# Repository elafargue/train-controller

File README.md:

train-controller
================

A Z scale model train controller with web interface.

You will find detailed instructions at http://www.aerodynes.org/ . This repository includes both hardware design files and the software you need to build the complete project.

The whole system is working well, and has been running for a long time on an actual layout.

Repository structure:

arduino: arduino sketches for the train controller hardware
hardware: schematics, boards (Eagle)
server: the node.js server that interfaces with the controller and serves the web app

Installation:

Please refer to http://www.aerodynes.org/ for detailed installation instructions. Below is a quick summary:

- Build the cape - Eagle files are included, all components are referenced in the design file, it is fairly straightforward.
- Install the arduino firmware on the cape: you can use the very good "ino" command line interface for doing so.
- Install Ubuntu Linux on your Beaglebone Black
- Install the latest nodejs distribution, and clone this repository
- Install mongodb (Ubuntu package is fine)
- Run "npm install" then "node server.js"
- ... you should be set!

Credits:

Thanks to the creators of the PID and aJson libraries (be sure to use the latest aJson library as I contributed patches to make it more robust).
Thanks to Christophe Coenraets for his great tutorials which were used as a base for the server

License:

All original code is placed under GPLv3 unless stated otherwise, see relevant license files where appropriate.

# Run as a service

Use `resources/train-controller.service` and copy it to `/etc/systemd/system`, then:

```
$ sudo systemctl daemon-reload
$ sudo systemctl enable train-controller
Created symlink /etc/systemd/system/multi-user.target.wants/train-controller.service → /etc/systemd/system/train-controller.service.
$ sudo service train-controller start
```

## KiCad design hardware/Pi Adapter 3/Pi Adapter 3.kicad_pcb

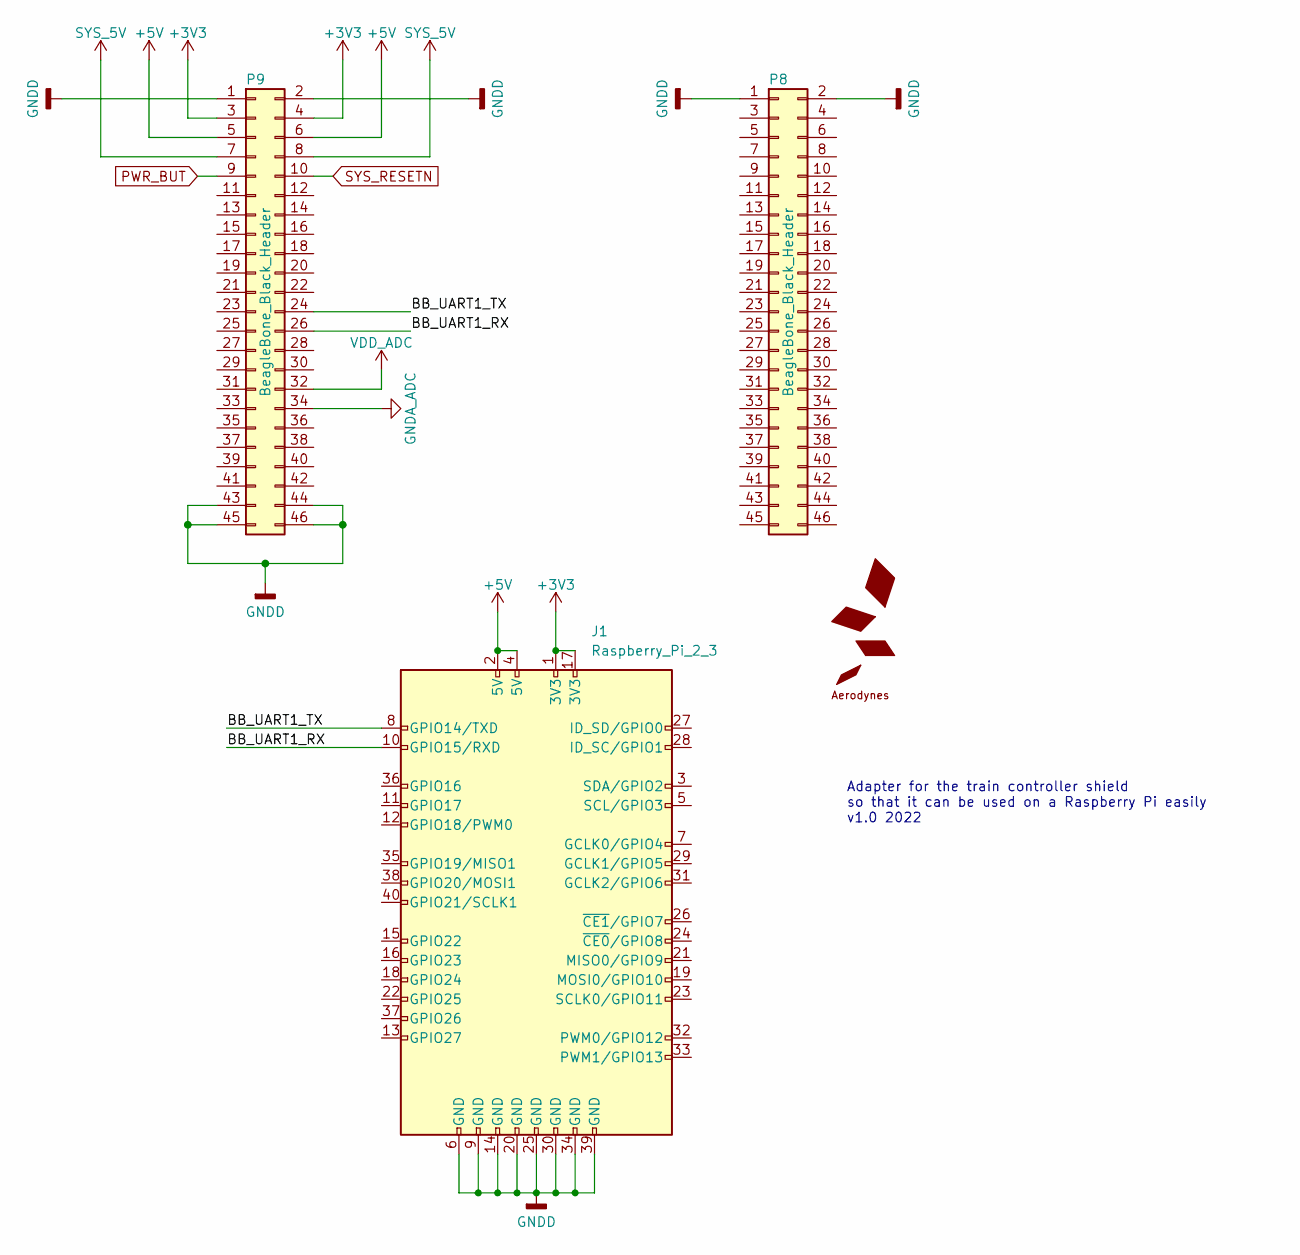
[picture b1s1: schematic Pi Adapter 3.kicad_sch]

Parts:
J1: Raspberry_Pi_2_3; PinSocket_2x20_P2.54mm_Vertical
M1: LOGO-AERODYNESSMALL; LOGO-AERODYNES-S
P8, P9: BeagleBone_Black_Header; Socket_BeagleBone_Black

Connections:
+3V3: J1.1 (3V3), J1.17 (3V3), P9.3, P9.4
+5V: J1.2 (5V), J1.4 (5V), P9.5, P9.6
/BB_UART1_RX: J1.10 (GPIO15/RXD), P9.26
/BB_UART1_TX: J1.8 (GPIO14/TXD), P9.24
GNDA_ADC: P9.34
GNDD: J1.6 (GND), J1.9 (GND), J1.14 (GND), J1.20 (GND), J1.25 (GND), J1.30 (GND), J1.34 (GND), J1.39 (GND), P8.1, P8.2, P9.1, P9.2, P9.43, P9.44, P9.45, P9.46
PWR_BUT: P9.9
SYS_5V: P9.7, P9.8
SYS_RESETN: P9.10
VDD_ADC: P9.32

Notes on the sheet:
Adapter for the train controller shield so that it can be used on a Raspberry Pi easily v1.0 2022

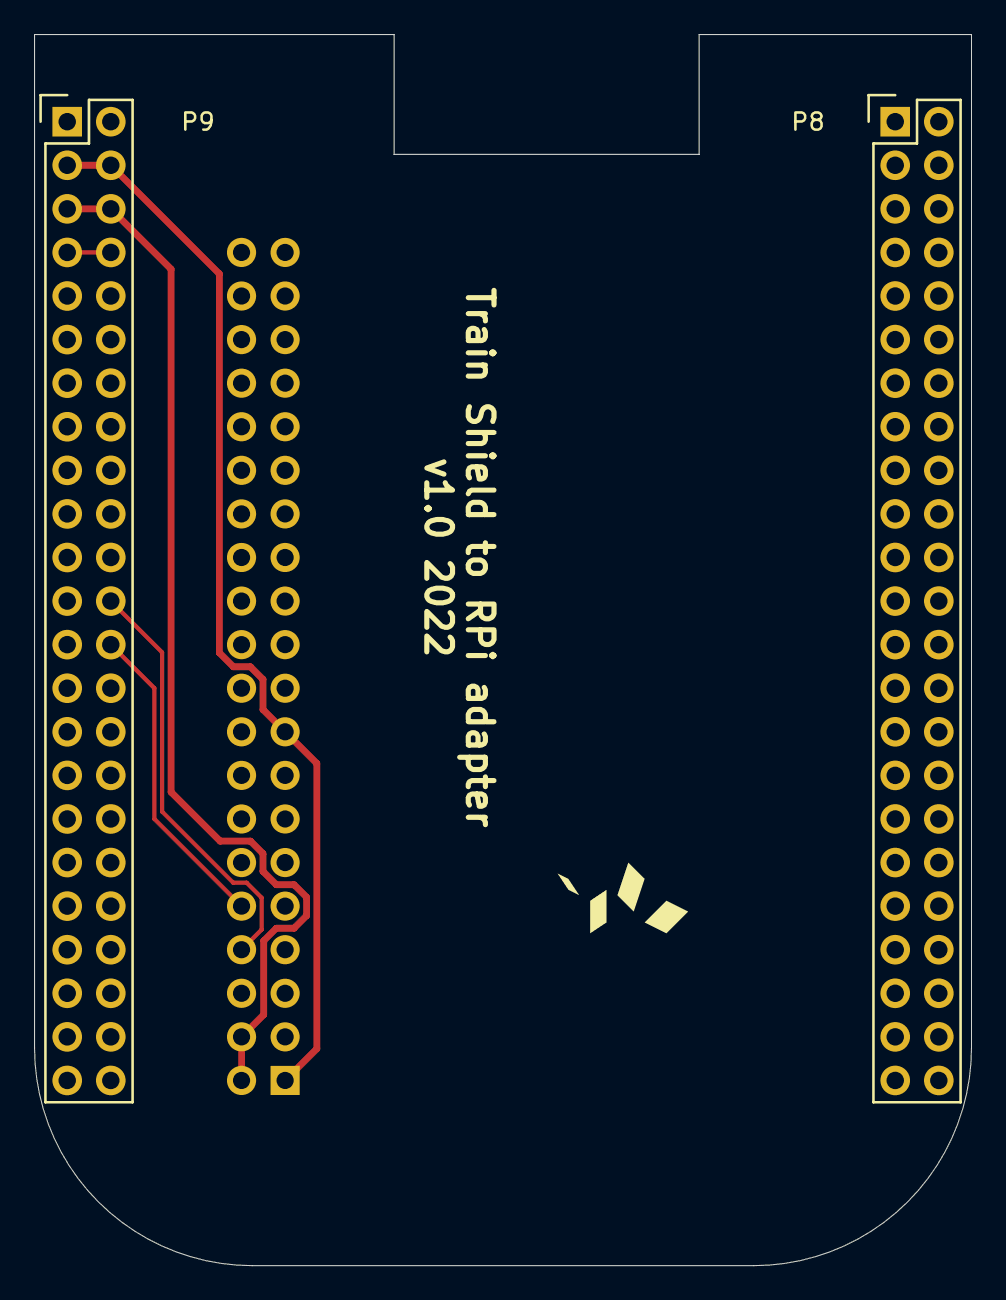
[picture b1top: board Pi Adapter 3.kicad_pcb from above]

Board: 2 copper layers, 54.6 x 71.7 mm, 4 parts (1 on the bottom side), 6 nets.

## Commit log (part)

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2013-02-07 Initial controller sketch for Arduino
2013-02-08 JSON and Hardware schematics
    This is untested so far. Added JSON support for both input and output
    on the controller, added simple schematics of the controller, updated
    .gitignore to exclude Eagle backup files.
2013-02-09 Working version of JSON interface
    The Arduino board tends to lose characters on the serial input,
    so more work is needed to make it more reliable. But it already
    works quite well.
2013-02-09 Lowered default speed, added free ram debug output
    Now seems to reliably get commands every time, since interrupts
    are now faster and serial speed slower. Also debugs the amount of
    free RAM in output if "DEBUG" is defined.
2013-02-09 Debug web page
    Added a debug.html web page to display controller parameters and graph
    them in real time. Only listens, does not send commands yet.
2013-02-09 Ignore more Mac-specific extensions
2013-02-10 Progress on web app
    Basic architecture for the web app. So far no real functionality, it is
    nearly identical to Christophe Coenraets' Wine Cellar. More to follow.
2013-02-10 Start using mongoose for database management
    Mongoose makes it much easier to manage the database. Migrated the
    locomotives to use it.
2013-02-10 Layouts defined and schema updated
    Progress on the schema for the application - still in flux - as well
    as a very basic layout browser.
2013-02-11 Manage settings on server through REST call /settings
    Implemented a single setting object on the database
2013-02-11 Select loco and layout
    Application now correctly selects locomotive and layout, and updates
    the settings. Settings page shows debug info on the settings object.
2013-02-12 General update of web app.
    In no particular order:
    - Layout/loco image drag and drop now works
    - Home view now is ready to update itself when loco and layouts are chosen
    - Settings view gives debugging and settings clear options
    - Better loco and layout list look and feel
2013-02-12 Enable Add Loco / Add Layout in Loco/Layout select screen
    Title says it all.
2013-02-13 Layout editor can now create and edit controllers
    Used a composite view since we can have many controllers on a single
    layout (might limit this later). Still details to iron out such as
    model validation before save for controller fields, etc.
2013-02-13 Further work on controller create/edit/delete from inside of layout view
    A bit tricky, but now it seems to be working fine every time.
2013-02-13 Forgot one file in previous commit
2013-02-17 Web app now talks to controller.
    Still work in progress, but initial messaging between web app and controller
    hardware is working, and several subviews can receive updates from the
    controller simultaneously.
    Error checking and overall robustness still to improve.
2013-02-21 Manage application settings properly
    Web app now manages settings/state using the same shared settings
    model between views (passed from appplicatino router on main.js), this
    way we get the correct change events, especially in the home view.
2013-02-22 Bug fixes
    - When adding a new logo and selecting the picture at the same time
    the picture was called "undefined" instead of loco Id. Fixed
    - Adding a new loco was not working because of reference to _id in
    template.
    - Removed references to localhost in all socket.io calls.
2013-02-22 Fix Graph initialisation + add License notices
    Finally fixed initialisation problem with flot. Also added GPL
    license info in the relevant places.
2013-02-24 Add feeback to direction buttons
2013-02-27 Add confirm delete button on both loco and layout managers
    Used bootbox.js as a helper library.
2013-03-01 Implement removeListener on link manager.
    So that entities like the loco controller don't get multiple
    subscriptions to the same event.
2013-03-01 Bug fix: switch to FuelUX caused edit loco and layout to fail.
    Also small progress on PID settings UI
2013-03-02 Backtrack: FuelUX did not work as well as expected.
    Used a dedicated bootstrap numeric spinner instead. More lightweight
    and actually works, whereas the FuelUX spinner did not work for decimal
    places at all - tons of weird bugs.
2013-03-04 Arduino sketch update: add command ack name
    The arduino controller now adds the command name to ack packets
    so that the server knows what it is acknowledging for.
2013-03-05 Add touch support for power control slider
    Now works fine with finger drag - and page does not scroll -
2013-03-05 Bugfix - when power=0, progress slider did not get updated
    was testing for value, not for isNaN...
2013-03-05 Don't glow non-clickable thumbnails
2013-03-05 Better usability on train controller - better user feedback
    Now various parts get enabled/disabled when they can/cannot be used.
2013-03-06 Web application support for accessories - start.
    Layouts can now manage a list of 'accessories' (turnouts, slips, etc). Those
    are saved in the database, and displayed on the layout image on the main screen.
    accessories can be dragged to their correct location on the layout image, and that
    location is saved in the database too.
2013-03-08 Bugfixing arduino sketch
    Latch values were wrong earlier.
2013-03-08 Improvements on layout edit view.
    Pressing "Enter" on a modal now triggers the default function (blue button)
    rather than just close the modal and do nothing. Fixed error in new accessory
    creation.
2013-03-08 Snap to grid when dragging accessories... but only works on Chrome somehow!
    I don't know what's going on with Firefox...
2013-03-08 Compute grid size based on percentage of layout image
    This way we get more consistent snap to grid for various window sizes.
2013-03-13 Manage uncouplers
    "Uncouplers" are special tracks for uncoupling cars. The layout details
    view can now configure an accessory to be an uncoupler, and attribute both
    address and port to the uncoupler. This way the same address can manage two
    uncoupler accessories and no I/O is wasted.
2013-03-14 Manage a log book for locomotives
    In the loco edit menu, you can now add/remove/edit logbook entries to keep
    track of maintenance tasks. Very simple logbook, nothing fancy.
    Note: I used backbone collections to manage the logbook entries, a bit different
    from what i have been doing with accessories and controllers so far. No major
    added interest, this method also means that we need to delete logbook entries
    manually whenever a locomotive is deleted. An alternative would be to manage a logbook
2013-03-17 Responsive design part 2
    Missed two files in last commit, typical.
2013-03-18 Big bugfix on hardware controller schematics and board.
    The 33880 pinout was reversed on my schematics...
2013-03-20 Final hardware version (Arduino shield) firmware working
    No current measurement yet though.
2013-03-20 Diagnostics view in web app
    Now that the harware can run power on tests and detect whether an accessory
    is connected or not, created a diags screen in the web app to display this.
2013-03-22 Diagnostics screen works now!
    Complete board diagnostics, including port open circuit detection.
2013-03-23 V1.0 Hardware - Arduino Shield as ordered on Seeed Studio
    Added the Eagle + Gerbers ordered on Seeed Studio - not tested yet
    obviously.
2013-03-25 Bug: could not add a new layout after latest changes to link manager
2013-04-02 Add last maintenance time in main screen.
2013-04-08 Start of Beaglebone cape
2013-04-08 Further work on backup of settings
2013-04-08 Debug output for server.js (raw Hex)
2013-04-09 Disable port diags if POST result is Fail for SPI
2013-04-09 Bugfix on opacity
2013-04-15 Updates to match exactly first working prototype
2013-04-15 Better port open status display on diag screen
    now uses a 1a/1b 2a/2b system, rather than counting from
    1 to 32, so this matches what's printed on the PCB...
2013-04-16 Backup and restore of configuration implemented, test in progress.
2013-05-05 Remove harcoded dependency on older socket.io lib.
2013-05-05 Use latest tarball snapshot of SerialPort
2013-05-13 Add test buttons on accessory settings
2013-05-13 Small typo corrections
2013-05-14 Add support for current sensor.
    All values output by the controller are now in real units (mV for BEMF
    and mA for current). Web app graphs current value. Better graphs (no
    gaps when sending turnout commands).
2013-05-15 Oops...
2013-05-16 Make graph axes the same color as the lines
    Now the user can understand which graph axis matches which line...
2013-05-16 Add Car management in the web app
    The cars manager is just a database of cars, does not (yet) have any
    use in running the layout.
2013-05-16 Set accessory pulse length upon controller connection
2013-05-22 Autosave runtime every 10 seconds when running a loco.
2013-05-22 Send PID params upon controller connection
2013-05-23 Bugfixes on log management And display log journal in loco details.
2013-05-28 Add view switcher + full screen graphs
    Refactoring: now uses a clean way to switch views with call to
    "onClose" function in the views, for proper cleanup.
    Added a "Full screen graph" view on Diagnostics screen.
2013-05-28 Cleanup on view switcher for all views
2013-06-26 Hardware controller: Beaglebone cape
    This is the working design - v3.0. Not fully debugged yet, but seems
    to be working fine so far.
2013-08-04 Various updates and bug fixes
2013-08-04 Relay query in accessory view: bugfixes
2013-08-19 Maintenance and improvements:
    Does not crash on DB server not running - just waits for it to come up.
    Better accessory settings handling when changing accessory type in settings.
    Cleaned up README and About.
2015-03-17 Node-serialport fixes for current version.
2015-03-17 Fix for CSS
2015-03-18 PouchDB fix: some numeric values are now returned as strings, use parseFloat.
2015-03-18 Arduino Sketch: fix auto accessory off (was not working properly, and accessories remained on forever).
2015-03-18 Accessory control bugfix (on was not sent)
2019-11-02 Bump underscore.string from 2.4.0 to 3.3.5 in /server
    Bumps [underscore.string](https://github.com/epeli/underscore.string) from 2.4.0 to 3.3.5.
    - [Release notes](https://github.com/epeli/underscore.string/releases)
    - [Changelog](https://github.com/epeli/underscore.string/blob/master/CHANGELOG.markdown)
    - [Commits](https://github.com/epeli/underscore.string/compare/2.4.0...3.3.5)
2022-04-10 Raspberry Pi adapter board to make the controller compatible with RPi 3
2025-08-14 More updates to HTML templates
2025-08-15 Restore proper views for the layout/loco/car lists
2025-08-15 Fix picture upload
2025-08-15 Restore ability to select a layout
2025-08-15 Improve accessory details view
2025-08-15 Add more bootstrap 5 upgrades
2025-08-15 Dark/Light mode support
2025-08-15 Working theme support
2025-08-15 Fix controller rendering
2025-08-15 Add a test controller, use with "TEST" as the port
2025-08-15 Implement serial port selection dropdown in controller details Create alerts if serial port open doesn't work as expected
2025-08-15 Remove MDB5 since it's not needed Finish (?) migration to Bootstrap 5 and remove unused CS Large update to all javascript dependencies, and serve them all locally Remove unused JavaScript libraries a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
2025-08-15 Fix display on small screens (mobile)
2025-08-15 Improve logbook display
2025-08-16 Don't let the name of the locomotives/car/layout names overflow
2025-08-16 Sort cars and locomotives by reference
    By numeric order
2025-08-16 Full upgrade (#2)
    * Claude: upgrade to Bootstrap 5, step 1
    * More updates to HTML templates
    * Further migration work
    * Restore proper views for the layout/loco/car lists
    * Fix picture upload
    * Add "Change Image" button for manual upload of images
2025-09-01 Display the locomotive image as a modal in loco details
